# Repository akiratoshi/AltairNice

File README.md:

This is a personal project inspired by the Altair AI03 & Sofle keyboard layout.
I’m using the Nice!Nano V2 to create a wireless version. 
This project marks my first attempt at designing a PCB, so I’ve kept it as simple as possible.

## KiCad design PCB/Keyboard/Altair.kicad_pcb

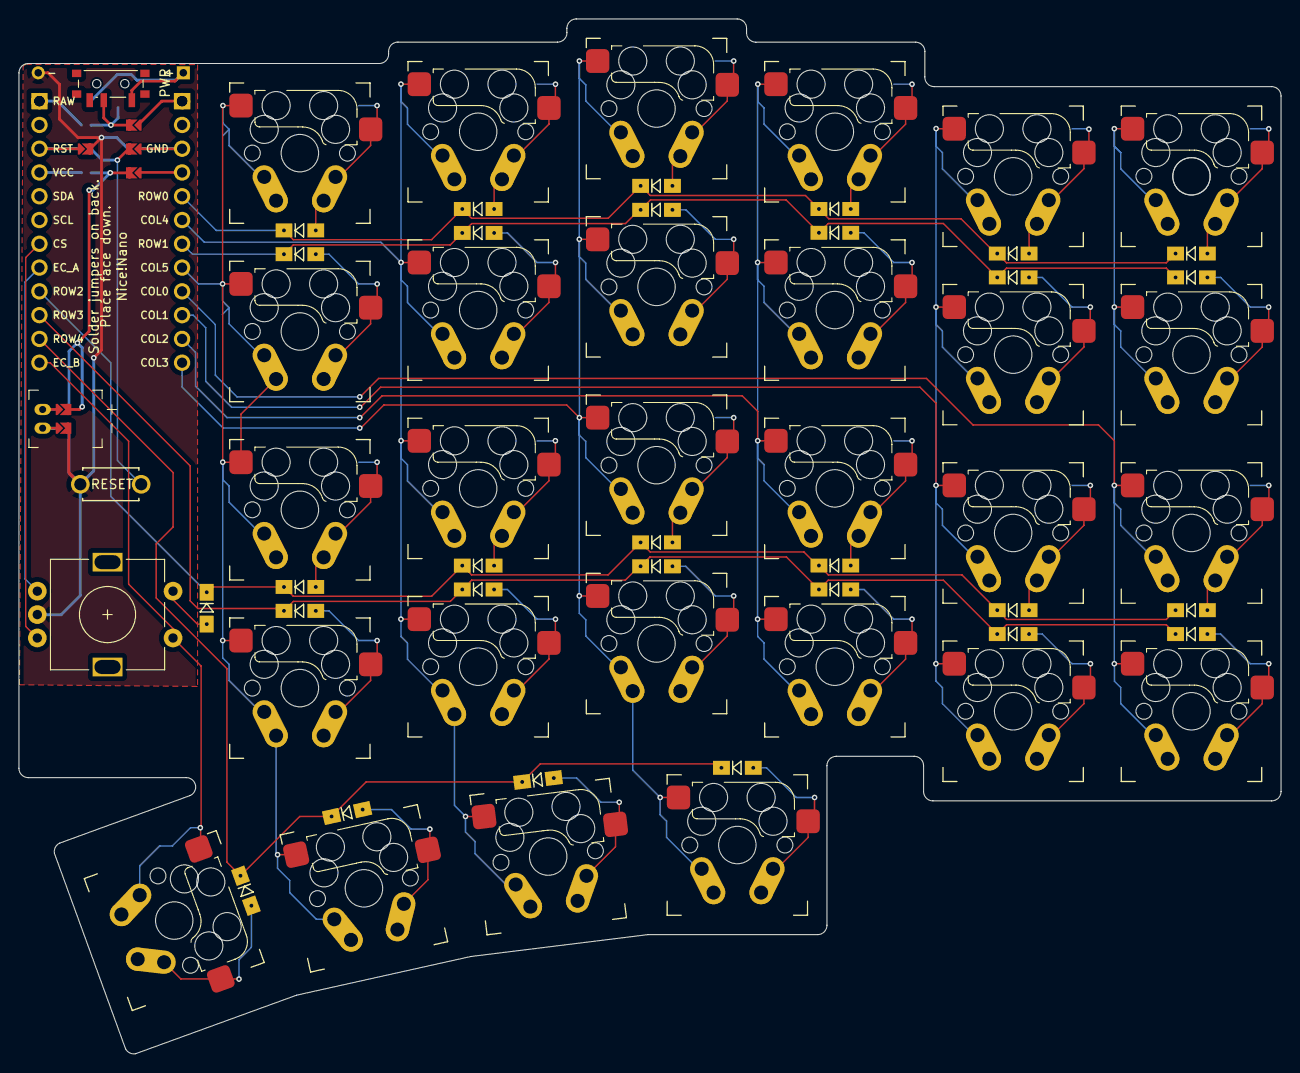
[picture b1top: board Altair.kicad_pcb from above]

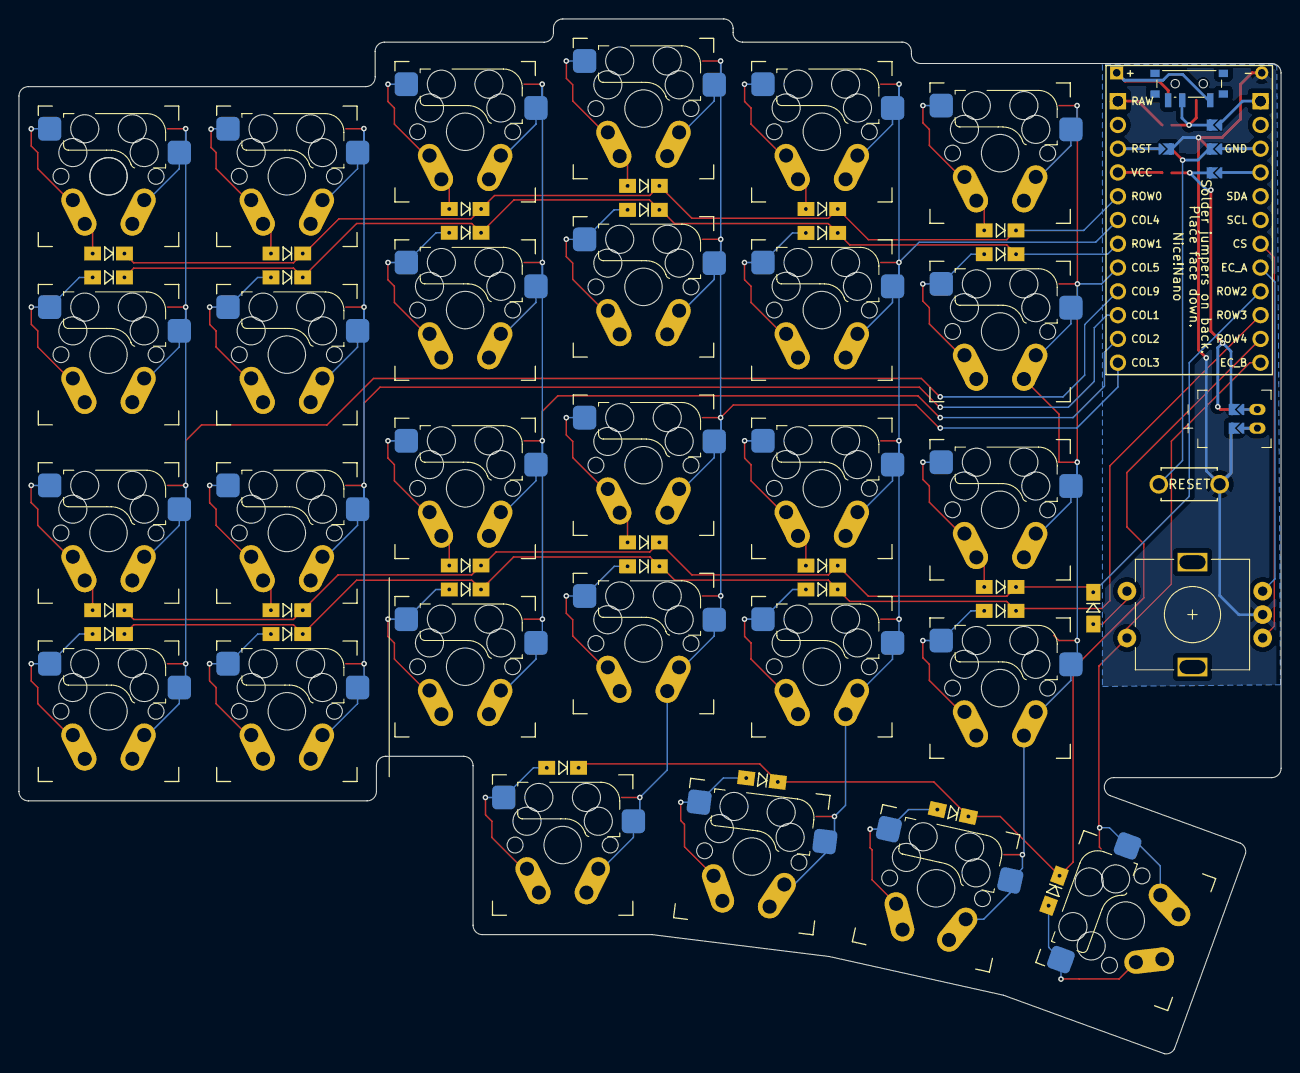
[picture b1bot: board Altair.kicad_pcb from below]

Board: 2 copper layers, 134.8 x 110.6 mm, 70 parts (31 on the bottom side), 53 nets.

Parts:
D1, D2, D3, D4, D5, D6, D7, D8, D9, D10, D11, D12, D13, D14, D15, D16, D17, D18, D19, D20, D21, D22, D23, D24, D25, D26, D27, D28, D98: D; Diode_SOD123
J1: Conn_01x02_Socket; battery_connector_jst_ph_2
J7, J8, J9, J10, J11, J12, J13, J14: Jumper
MCU1: ProMicro
PWR: SW_Nidec_CAS-120A1; sw_power
SW1, SW2, SW3, SW4, SW5, SW6, SW7, SW8, SW9, SW10, SW11, SW12, SW13, SW14, SW15, SW16, SW17, SW18, SW19, SW20, SW21, SW22, SW23, SW24, SW25, SW26, SW27, SW28: SW_Push; SW_MX_HotSwap_THT_double
SW98: RotaryEncoder_Switch; RotaryEncoder_Alps_EC11E-Switch_Vertical_H20mm-keebio_modif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
SW99: SW_Push; ResetSW

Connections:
COL0: MCU1.9, SW1.1, SW7.1, SW13.1, SW19.1
COL1: MCU1.10, SW2.1, SW8.1, SW14.1, SW20.1
COL2: MCU1.11, SW3.1, SW9.1, SW15.1, SW21.1
COL3: MCU1.12, SW4.1, SW10.1, SW16.1, SW22.1, SW25.1
COL4: MCU1.6, SW5.1, SW11.1, SW17.1, SW23.1, SW26.1
COL5: MCU1.8, SW6.1, SW12.1, SW18.1, SW24.1, SW27.1
COL6: MCU1.24, SW28.1, SW98.S1
EC_A: MCU1.20, SW98.A
EC_B: MCU1.19, SW98.B
GND: J1.1, J1.2, J10.2, J14.2, SW98.C, SW99.2
GND_RST: J8.1, J14.1, MCU1.15
GND_VCC: J9.1, MCU1.16
unnamed: D1.2, SW1.2
unnamed: D2.2, SW2.2
unnamed: D3.2, SW3.2
unnamed: D4.2, SW4.2
unnamed: D5.2, SW5.2
unnamed: D6.2, SW6.2
unnamed: D7.2, SW7.2
unnamed: D8.2, SW8.2
unnamed: D9.2, SW9.2
unnamed: D10.2, SW10.2
unnamed: D11.2, SW11.2
unnamed: D12.2, SW12.2
unnamed: D13.2, SW13.2
unnamed: D14.2, SW14.2
unnamed: D15.2, SW15.2
unnamed: D16.2, SW16.2
unnamed: D17.2, SW17.2
unnamed: D18.2, SW18.2
unnamed: D19.2, SW19.2
unnamed: D20.2, SW20.2
unnamed: D21.2, SW21.2
unnamed: D22.2, SW22.2
unnamed: D23.2, SW23.2
unnamed: D24.2, SW24.2
unnamed: D25.2, SW25.2
unnamed: D26.2, SW26.2
unnamed: D27.2, SW27.2
unnamed: D28.2, SW28.2
unnamed: D98.2 (A), SW98.S2
P1_RAW: J7.1, MCU1.13
RAW: J7.2, J11.2, PWR.2
RAW_P1: J11.1, MCU1.1
ROW0: D1.1, D2.1, D3.1, D4.1, D5.1, D6.1, MCU1.5
ROW1: D7.1, D8.1, D9.1, D10.1, D11.1, D12.1, MCU1.7
ROW2: D13.1, D14.1, D15.1, D16.1, D17.1, D18.1, D98.1 (K), MCU1.21
ROW3: D19.1, D20.1, D21.1, D22.1, D23.1, D24.1, MCU1.22
ROW4: D25.1, D26.1, D27.1, D28.1, MCU1.23
RST: J8.2, J12.2, SW99.1
RST_GND: J10.1, J12.1, MCU1.3
VCC: J1.1, J1.2, J9.2, J13.2
VCC_GND: J13.1, MCU1.4

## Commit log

2024-11-03 Remove Led
2024-11-03 Remove onoff button
2024-11-03 Change Diode Footprint to make new way routing
2024-11-05 Done routing for SW
2024-11-05 Done for 1 side PCB
2024-11-07 add 2 MCU
2024-11-10 Finish PCB
2024-11-10 Initial
2024-11-10 Add init firmware
2024-11-10 test
2024-11-10 Remove firmware
2024-11-17 Create V1 base on Sofle V2
2024-12-07 Change to reverse version, del all previous version
2024-12-07 add hs reverse fp
2024-12-08 Done outline and fp for mcu/switch
2024-12-15 routing sw
2024-12-15 inprocessing
2024-12-15 add sample
2024-12-19 inprocess
2024-12-21 Bỏ qua các thư mục PCB/footprint và PCB/Keyboard/Altair-backups
2024-12-21 done & clean
2024-12-21 Update .gitignore and remove ignored files
2024-12-21 Cleaned
2024-12-27 ajust plate
